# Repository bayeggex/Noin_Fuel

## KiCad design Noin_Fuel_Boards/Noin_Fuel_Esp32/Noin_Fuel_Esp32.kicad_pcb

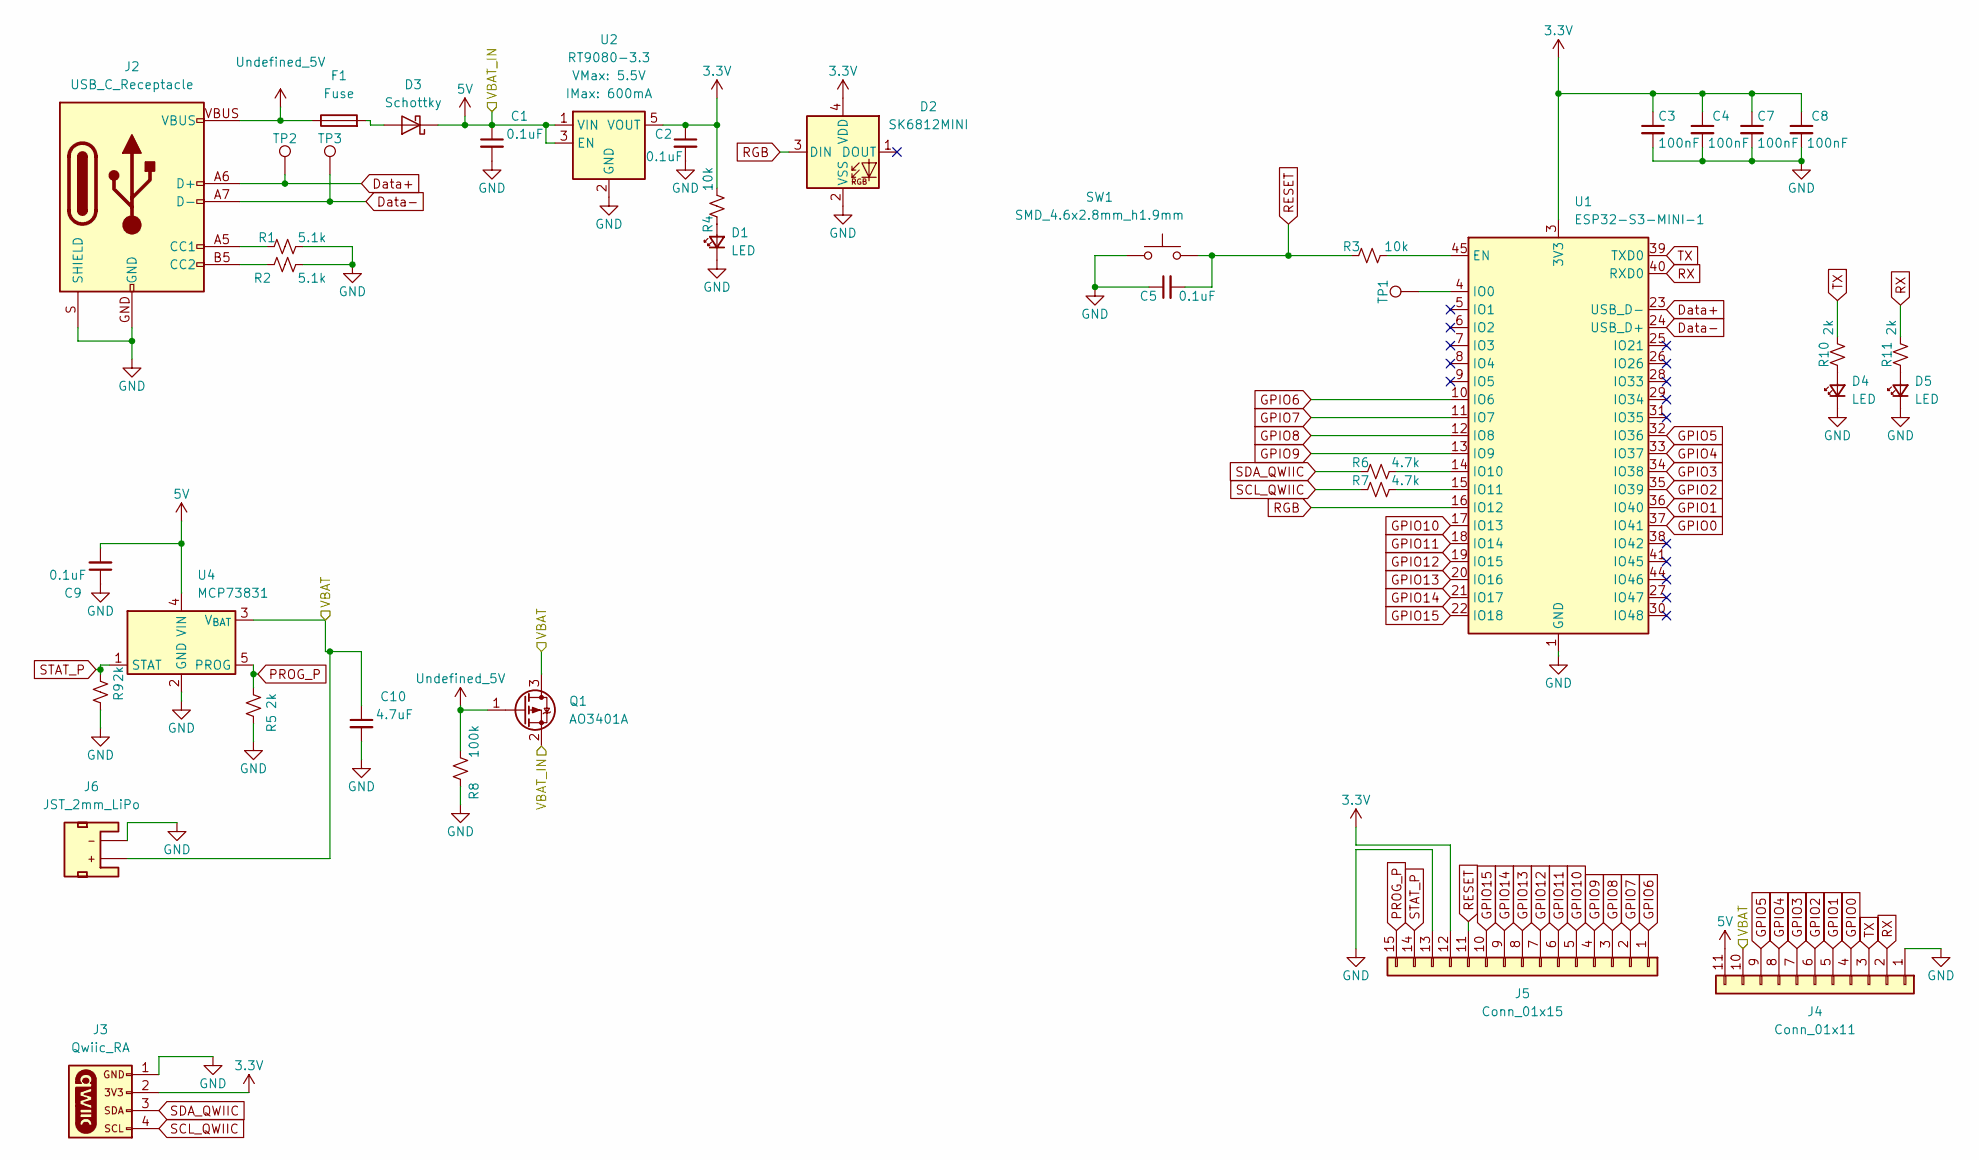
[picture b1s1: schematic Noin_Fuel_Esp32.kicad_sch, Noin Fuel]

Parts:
C1, C2, C5, C9: 0.1uF; C_0402_1005Metric; Voltage 25V; Tolerance 20%
C3, C4, C7, C8: 100nF; C_0402_1005Metric; Voltage 25V; Tolerance 20%
C10: 4.7uF; C_0402_1005Metric; Voltage 25V; Tolerance 20%
D1, D4, D5: LED; LED_0603_1608Metric
D2: SK6812MINI; LED_SK6812MINI_PLCC4_3.5x3.5mm_P1.75mm
D3: Schottky; Diode_Schottky_0603
F1: Fuse; Fuse_0603_1608Metric
J2: USB_C_Receptacle; USB-C_16
J3: Qwiic_RA; JST_1x04_P1.0mm_Horizontal_SMD
J4: Conn_01x11; 1x11_P2.54mm
J5: Conn_01x15; 1x15
J6: JST_2mm_LiPo; JST_1x02_P2.0mm_Horizontal_SMD
Q1: AO3401A; SOT-23
R1, R2: 5.1k; R_0402_1005Metric
R3, R4: 10k; R_0402_1005Metric
R5, R9, R10, R11: 2k; R_0402_1005Metric
R6, R7: 4.7k; R_0402_1005Metric
R8: 100k; R_0402_1005Metric
SW1: SMD_4.6x2.8mm_h1.9mm; Push_SMD_4.6x2.8mm_h1.9mm
TP1, TP2, TP3: 0.5mm; TestPoint-0.5mm
U1: ESP32-S3-MINI-1; ESP32-S2-MINI-1
U2: RT9080-3.3; SOT23-5
U4: MCP73831; SOT23-5

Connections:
3.3V: C2.1, C3.1, C4.1, C7.1, C8.1, D2.4 (VDD), J3.2, J5.12, R4.2, U1.3 (3V3), U2.5 (VOUT)
5V: C1.1, C9.2, D3.1 (K), J4.11, Q1.2 (S), U2.1 (VIN), U2.3 (EN), U4.4 (VIN)
/VBAT: C10.1, J4.10, J6.2 (+), Q1.3 (D), U4.3 (V_{BAT})
Data+: J2.A6 (D+), J2.B6 (D+), TP2.1, U1.23 (USB_D-)
Data-: J2.A7 (D-), J2.B7 (D-), TP3.1, U1.24 (USB_D+)
GND: C1.2, C2.2, C3.2, C4.2, C5.1, C7.2, C8.2, C9.1, C10.2, D1.1 (K), D2.2 (VSS), D4.1 (K), D5.1 (K), J2.GND, J2.S (SHIELD), J3.1, J4.1, J5.13, J6.1 (-), R1.2, R2.1, R5.2, R8.2, R9.2, SW1.1, U1.1 (GND), U1.2 (GND), U1.42 (GND), U1.43 (GND), U1.46 (GND), U1.47 (GND), U1.48 (GND), U1.49 (GND), U1.50 (GND), U1.51 (GND), U1.52 (GND), U1.53 (GND), U1.54 (GND), U1.55 (GND), U1.56 (GND), U1.57 (GND), U1.58 (GND), U1.59 (GND), U1.60 (GND), U1.61 (GND), U1.62 (GND), U1.63 (GND), U1.64 (GND), U1.65 (GND), U2.2 (GND), U4.2 (GND)
GPIO0: J4.4, U1.37 (IO41)
GPIO1: J4.5, U1.36 (IO40)
GPIO2: J4.6, U1.35 (IO39)
GPIO3: J4.7, U1.34 (IO38)
GPIO4: J4.8, U1.33 (IO37)
GPIO5: J4.9, U1.32 (IO36)
GPIO6: J5.1, U1.10 (IO6)
GPIO7: J5.2, U1.11 (IO7)
GPIO8: J5.3, U1.12 (IO8)
GPIO9: J5.4, U1.13 (IO9)
GPIO10: J5.5, U1.17 (IO13)
GPIO11: J5.6, U1.18 (IO14)
GPIO12: J5.7, U1.19 (IO15)
GPIO13: J5.8, U1.20 (IO16)
GPIO14: J5.9, U1.21 (IO17)
GPIO15: J5.10, U1.22 (IO18)
unnamed: D1.2 (A), R4.1
unnamed: D3.2 (A), F1.2
unnamed: D4.2 (A), R10.1
unnamed: D5.2 (A), R11.1
unnamed: J2.A5 (CC1), R1.1
unnamed: J2.B5 (CC2), R2.2
unnamed: R3.2, U1.45 (EN)
unnamed: TP1.1, U1.4 (IO0)
unnamed: R6.2, U1.14 (IO10)
unnamed: R7.2, U1.15 (IO11)
PROG_P: J5.15, R5.1, U4.5 (PROG)
RESET: C5.2, J5.11, R3.1, SW1.2
RGB: D2.3 (DIN), U1.16 (IO12)
RX: J4.2, R11.2, U1.40 (RXD0)
SCL_QWIIC: J3.4, R7.1
SDA_QWIIC: J3.3, R6.1
STAT_P: J5.14, R9.1, U4.1 (STAT)
TX: J4.3, R10.2, U1.39 (TXD0)
Undefined_5V: F1.1, J2.VBUS, Q1.1 (G), R8.1

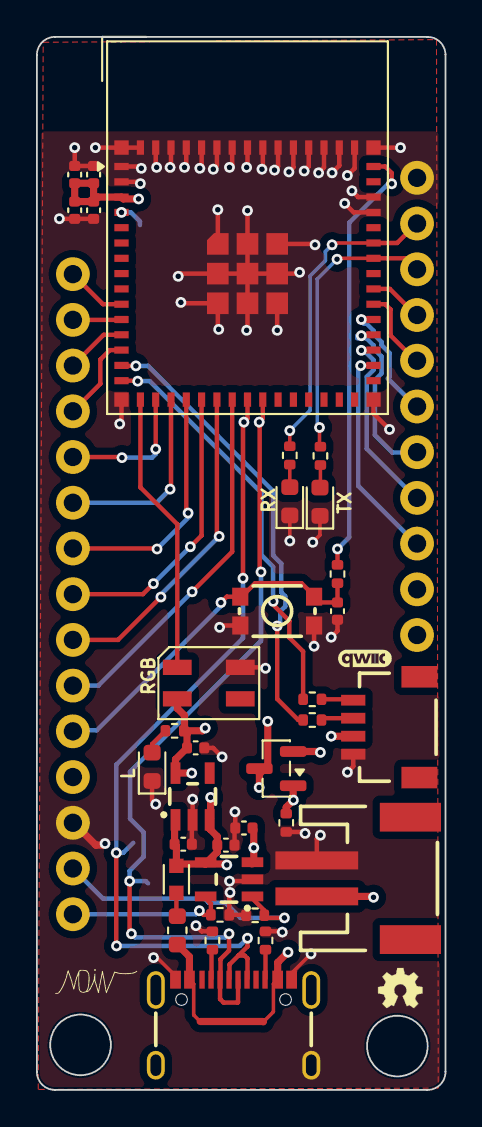
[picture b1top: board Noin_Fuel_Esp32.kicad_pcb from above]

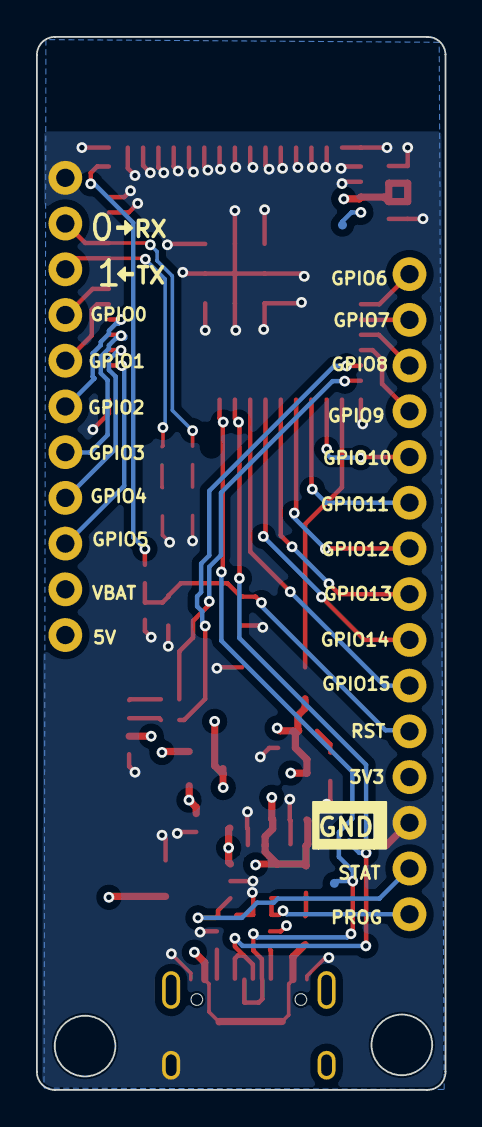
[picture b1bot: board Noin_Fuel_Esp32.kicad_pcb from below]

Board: 4 copper layers, 22.7 x 58.5 mm, 40 parts (3 on the bottom side), 41 nets.

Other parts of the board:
Ref**: Val**; OSHW_Logo_2.5mm

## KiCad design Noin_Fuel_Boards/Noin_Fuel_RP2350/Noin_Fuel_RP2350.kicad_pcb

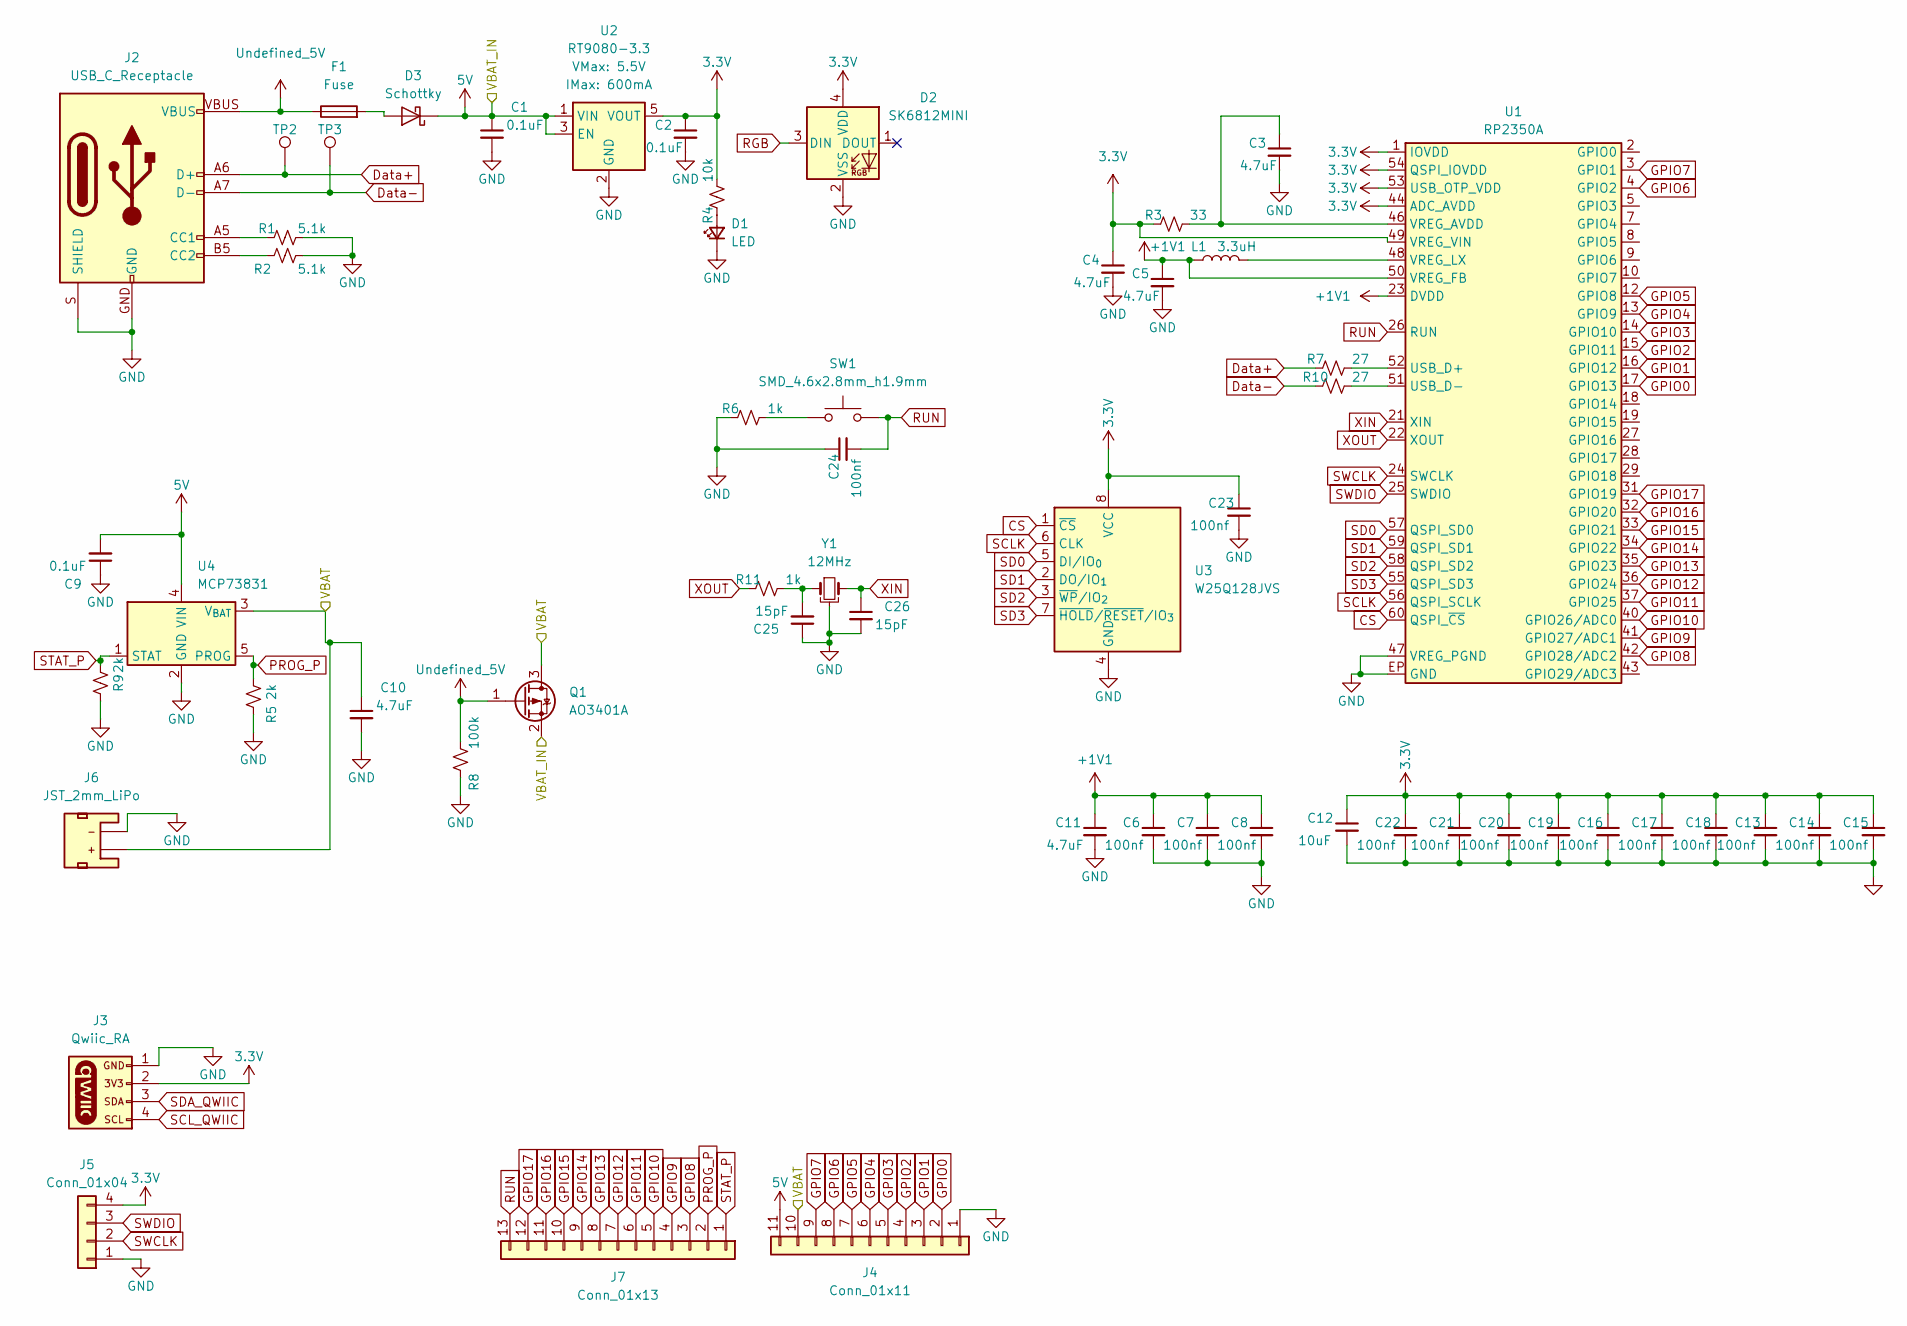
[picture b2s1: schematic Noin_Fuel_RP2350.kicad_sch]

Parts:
C1, C2, C9: 0.1uF; C_0402_1005Metric; Voltage 25V; Tolerance 20%
C3, C4, C5, C10, C11: 4.7uF; C_0402_1005Metric; Voltage 25V; Tolerance 20%
C6, C7, C8, C13, C14, C15, C16, C17, C18, C19, C20, C21, C22, C23, C24: 100nf; C_0402_1005Metric; Voltage 25V; Tolerance 20%
C12: 10uF; C_0402_1005Metric; Voltage 25V; Tolerance 20%
C25, C26: 15pF; C_0402_1005Metric; Voltage 25V; Tolerance 20%
D1: LED; LED_0603_1608Metric
D2: SK6812MINI; LED_SK6812MINI_PLCC4_3.5x3.5mm_P1.75mm
D3: Schottky; Diode_Schottky_0603
F1: Fuse; Fuse_0603_1608Metric
J2: USB_C_Receptacle; USB-C_16
J3: Qwiic_RA; JST_1x04_P1.0mm_Horizontal_SMD
J4: Conn_01x11; 1x11_P2.54mm
J5: Conn_01x04; 1x04_P2.54mm
J6: JST_2mm_LiPo; JST_1x02_P2.0mm_Horizontal_SMD
J7: Conn_01x13; 1x13
L1: 3.3uH; L_0402_1005Metric
Q1: AO3401A; SOT-23
R1, R2: 5.1k; R_0402_1005Metric
R3: 33; R_0402_1005Metric
R4: 10k; R_0402_1005Metric
R5, R9: 2k; R_0402_1005Metric
R6, R11: 1k; R_0402_1005Metric
R7, R10: 27; R_0402_1005Metric
R8: 100k; R_0402_1005Metric
SW1: SMD_4.6x2.8mm_h1.9mm; Push_SMD_4.6x2.8mm_h1.9mm
TP2, TP3: 0.5mm; TestPoint-0.5mm
U1: RP2350A; QFN-60-1EP_7x7mm_P0.4mm_EP3.5x3.5mm
U2: RT9080-3.3; SOT23-5
U3: W25Q128JVS; SOIC-8_5.3x5.3mm_P1.27mm
U4: MCP73831; SOT23-5
Y1: 12MHz; Crystal_SMD_2.5x2.0mm

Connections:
3.3V: C2.1, C4.1, C12.1, C13.1, C14.1, C15.1, C16.1, C17.1, C18.1, C19.1, C20.1, C21.1, C22.1, C23.1, D2.4 (VDD), J3.2, J5.4, R3.1, R4.2, U1.1 (IOVDD), U1.11 (IOVDD), U1.20 (IOVDD), U1.30 (IOVDD), U1.38 (IOVDD), U1.44 (ADC_AVDD), U1.45 (IOVDD), U1.49 (VREG_VIN), U1.53 (USB_OTP_VDD), U1.54 (QSPI_IOVDD), U2.5 (VOUT), U3.8 (VCC)
5V: C1.1, C9.2, D3.1 (K), J4.11, Q1.2 (S), U2.1 (VIN), U2.3 (EN), U4.4 (VIN)
+1V1: C5.1, C6.1, C7.1, C8.1, C11.1, L1.1, U1.6 (DVDD), U1.23 (DVDD), U1.39 (DVDD), U1.50 (VREG_FB)
/VBAT: C10.1, J4.10, J6.2 (+), Q1.3 (D), U4.3 (V_{BAT})
CS: U1.60 (QSPI_~CS), U3.1 (~CS)
Data+: J2.A6 (D+), J2.B6 (D+), R7.1, TP2.1 (1_1)
Data-: J2.A7 (D-), J2.B7 (D-), R10.1, TP3.1 (1_1)
GND: C1.2, C2.2, C3.2, C4.2, C5.2, C6.2, C7.2, C8.2, C9.1, C10.2, C11.2, C12.2, C13.2, C14.2, C15.2, C16.2, C17.2, C18.2, C19.2, C20.2, C21.2, C22.2, C23.2, C24.1, C25.1, C26.2, D1.1 (K), D2.2 (VSS), J2.GND, J2.S (SHIELD), J3.1, J4.1, J5.1, J6.1 (-), R1.2, R2.1, R5.2, R6.1, R8.2, R9.2, U1.47 (VREG_PGND), U1.EP (GND), U2.2 (GND), U3.4 (GND), U4.2 (GND), Y1.2, Y1.4
GPIO0: J4.2, U1.17 (GPIO13)
GPIO1: J4.3, U1.16 (GPIO12)
GPIO2: J4.4, U1.15 (GPIO11)
GPIO3: J4.5, U1.14 (GPIO10)
GPIO4: J4.6, U1.13 (GPIO9)
GPIO5: J4.7, U1.12 (GPIO8)
GPIO6: J4.8, U1.4 (GPIO2)
GPIO7: J4.9, U1.3 (GPIO1)
GPIO8: J7.3, U1.42 (GPIO28/ADC2)
GPIO9: J7.4, U1.41 (GPIO27/ADC1)
GPIO10: J7.5, U1.40 (GPIO26/ADC0)
GPIO11: J7.6, U1.37 (GPIO25)
GPIO12: J7.7, U1.36 (GPIO24)
GPIO13: J7.8, U1.35 (GPIO23)
GPIO14: J7.9, U1.34 (GPIO22)
GPIO15: J7.10, U1.33 (GPIO21)
GPIO16: J7.11, U1.32 (GPIO20)
GPIO17: J7.12, U1.31 (GPIO19)
unnamed: C25.2, R11.2, Y1.1
unnamed: D1.2 (A), R4.1
unnamed: D3.2 (A), F1.2
unnamed: J2.A5 (CC1), R1.1
unnamed: J2.B5 (CC2), R2.2
unnamed: R6.2, SW1.1
unnamed: R7.2, U1.52 (USB_D+)
unnamed: R10.2, U1.51 (USB_D-)
unnamed: C3.1, R3.2, U1.46 (VREG_AVDD)
unnamed: L1.2, U1.48 (VREG_LX)
PROG_P: J7.2, R5.1, U4.5 (PROG)
RGB: D2.3 (DIN)
RUN: C24.2, J7.13, SW1.2, U1.26 (RUN)
SCLK: U1.56 (QSPI_SCLK), U3.6 (CLK)
SCL_QWIIC: J3.4
SD0: U1.57 (QSPI_SD0), U3.5 (DI/IO_{0})
SD1: U1.59 (QSPI_SD1), U3.2 (DO/IO_{1})
SD2: U1.58 (QSPI_SD2), U3.3 (~WP/IO_{2})
SD3: U1.55 (QSPI_SD3), U3.7 (~HOLD/~RESET/IO_{3})
SDA_QWIIC: J3.3
STAT_P: J7.1, R9.1, U4.1 (STAT)
SWCLK: J5.2, U1.24 (SWCLK)
SWDIO: J5.3, U1.25 (SWDIO)
Undefined_5V: F1.1, J2.VBUS, Q1.1 (G), R8.1
XIN: C26.1, U1.21 (XIN), Y1.3
XOUT: R11.1, U1.22 (XOUT)

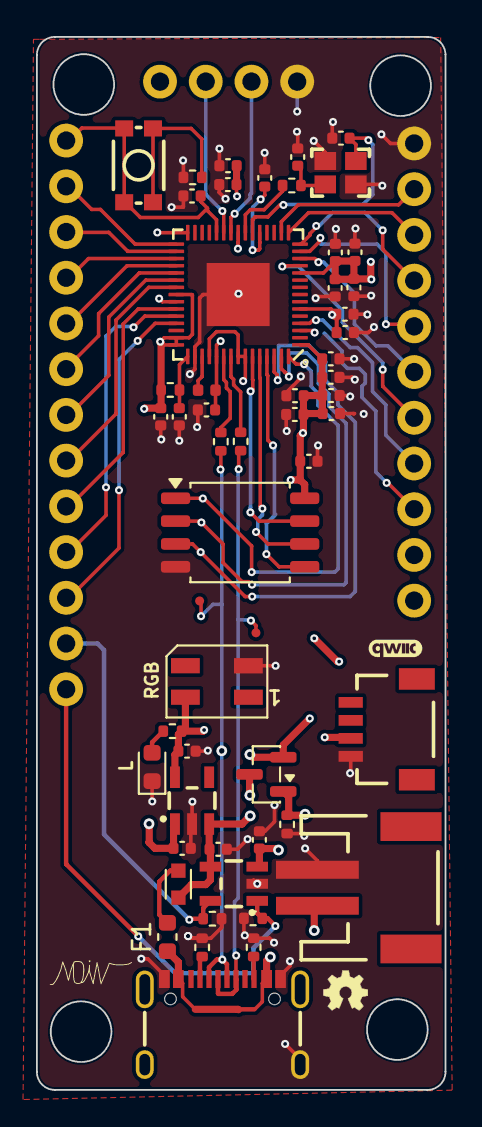
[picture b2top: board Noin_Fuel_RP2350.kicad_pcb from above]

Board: 4 copper layers, 22.7 x 58.5 mm, 58 parts (0 on the bottom side), 49 nets.

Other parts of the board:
Ref**: Val**; OSHW_Logo_2.5mm

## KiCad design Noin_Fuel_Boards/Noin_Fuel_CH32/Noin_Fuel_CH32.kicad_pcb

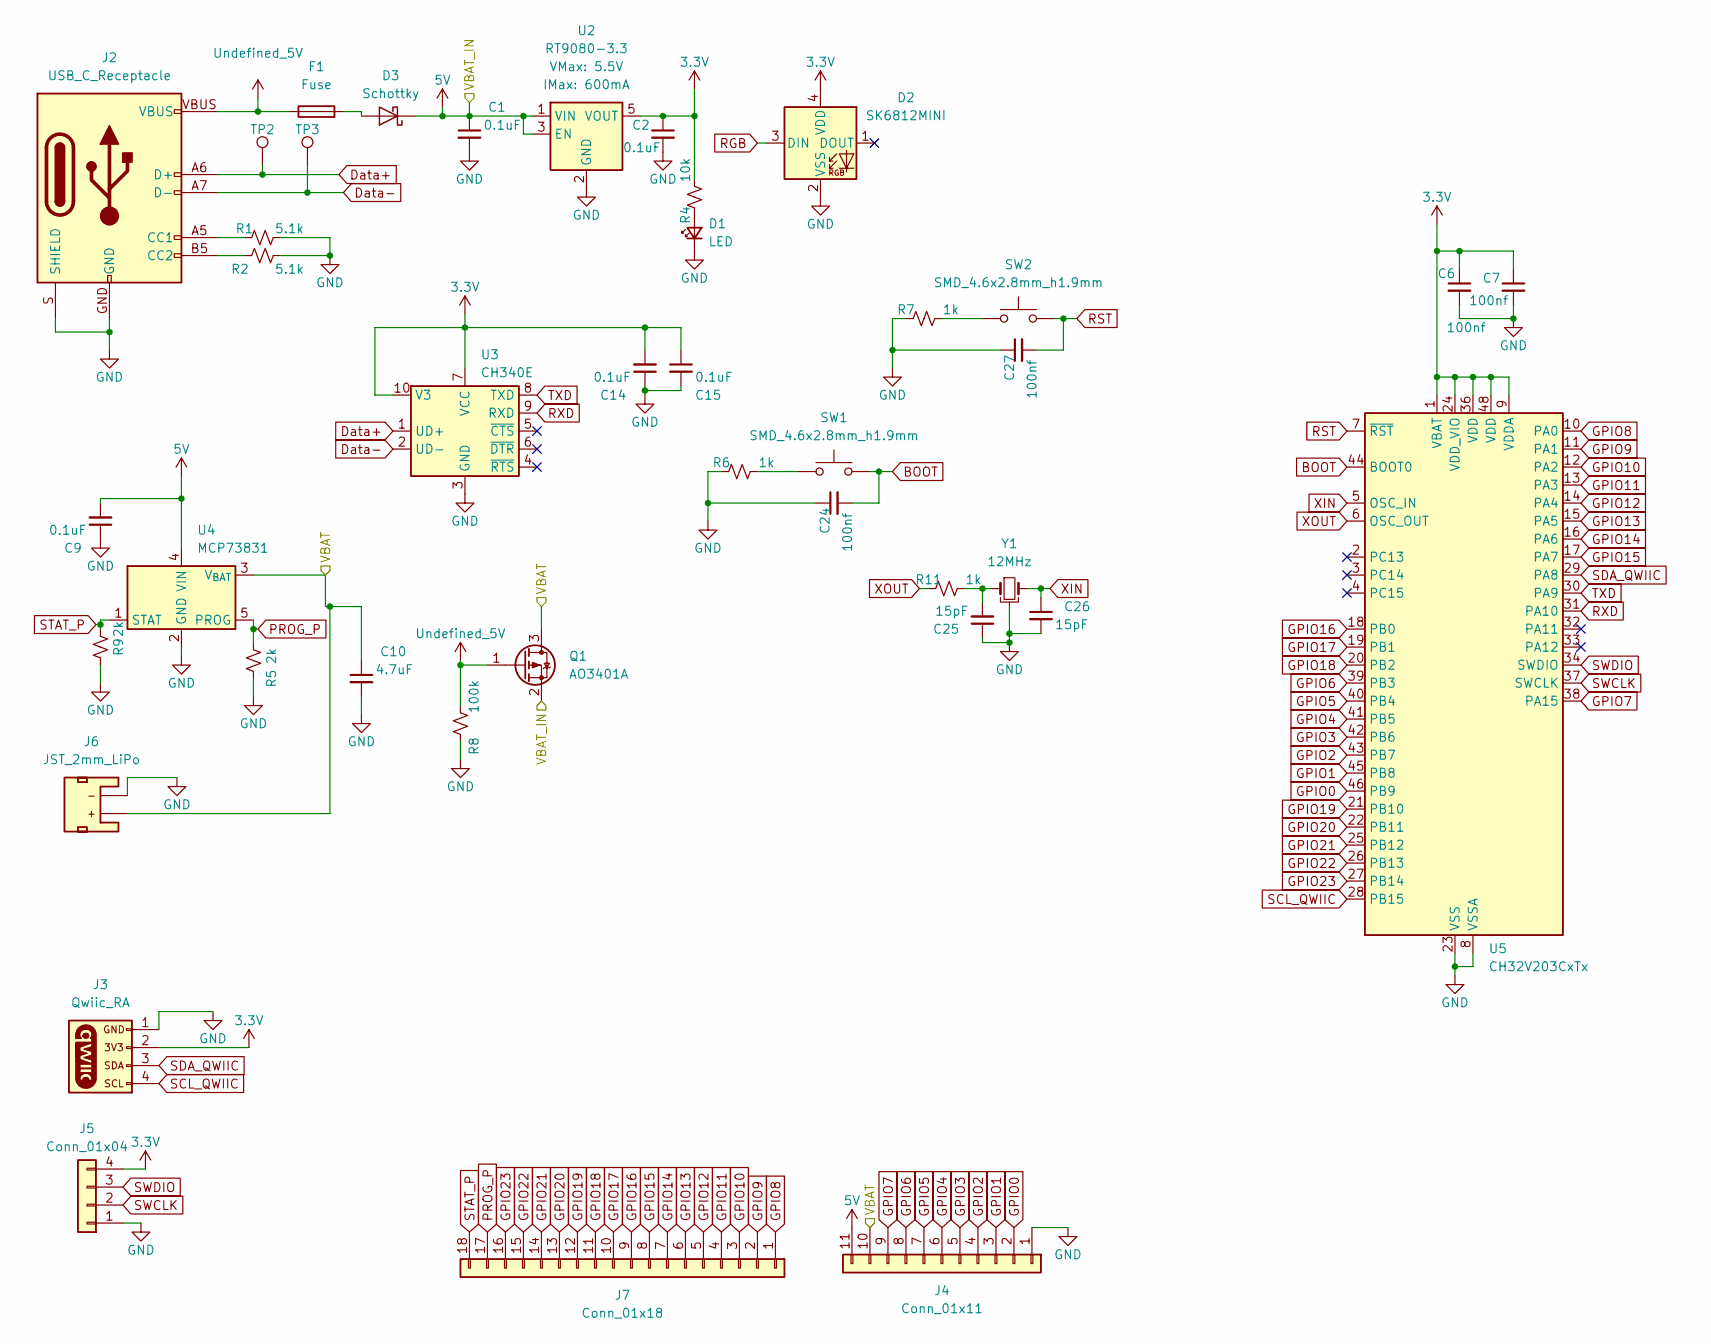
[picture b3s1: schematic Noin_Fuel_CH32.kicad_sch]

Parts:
C1, C2, C9, C14, C15: 0.1uF; C_0402_1005Metric; Voltage 25V; Tolerance 20%
C6, C7, C24, C27: 100nf; C_0402_1005Metric; Voltage 25V; Tolerance 20%
C10: 4.7uF; C_0402_1005Metric; Voltage 25V; Tolerance 20%
C25, C26: 15pF; C_0402_1005Metric; Voltage 25V; Tolerance 20%
D1: LED; LED_0603_1608Metric
D2: SK6812MINI; LED_SK6812MINI_PLCC4_3.5x3.5mm_P1.75mm
D3: Schottky; Diode_Schottky_0603
F1: Fuse; Fuse_0603_1608Metric
J2: USB_C_Receptacle; USB-C_16
J3: Qwiic_RA; JST_1x04_P1.0mm_Horizontal_SMD
J4: Conn_01x11; 1x11_P2.54mm
J5: Conn_01x04; 1x04_P2.54mm
J6: JST_2mm_LiPo; JST_1x02_P2.0mm_Horizontal_SMD
J7: Conn_01x18; 1x18
Q1: AO3401A; SOT-23
R1, R2: 5.1k; R_0402_1005Metric
R4: 10k; R_0402_1005Metric
R5, R9: 2k; R_0402_1005Metric
R6, R7, R11: 1k; R_0402_1005Metric
R8: 100k; R_0402_1005Metric
SW1, SW2: SMD_4.6x2.8mm_h1.9mm; Push_SMD_4.6x2.8mm_h1.9mm
TP2, TP3: 0.5mm; TestPoint-0.5mm
U2: RT9080-3.3; SOT23-5
U3: CH340E; MSOP-10_3x3mm_P0.5mm
U4: MCP73831; SOT23-5
U5: CH32V203CxTx; LQFP-48_7x7mm_P0.5mm
Y1: 12MHz; Crystal_SMD_2.5x2.0mm

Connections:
3.3V: C2.1, C6.1, C7.1, C14.2, C15.1, D2.4 (VDD), J3.2, J5.4, R4.2, U2.5 (VOUT), U3.7 (VCC), U3.10 (V3), U5.1 (VBAT), U5.9 (VDDA), U5.24 (VDD_VIO), U5.36 (VDD), U5.48 (VDD)
5V: C1.1, C9.2, D3.1 (K), J4.11, Q1.2 (S), U2.1 (VIN), U2.3 (EN), U4.4 (VIN)
/VBAT: C10.1, J4.10, J6.2 (+), Q1.3 (D), U4.3 (V_{BAT})
BOOT: C24.2, SW1.2, U5.44 (BOOT0)
Data+: J2.A6 (D+), J2.B6 (D+), TP2.1 (1_1), U3.1 (UD+)
Data-: J2.A7 (D-), J2.B7 (D-), TP3.1 (1_1), U3.2 (UD-)
GND: C1.2, C2.2, C6.2, C7.2, C9.1, C10.2, C14.1, C15.2, C24.1, C25.1, C26.2, C27.1, D1.1 (K), D2.2 (VSS), J2.GND, J2.S (SHIELD), J3.1, J4.1, J5.1, J6.1 (-), R1.2, R2.1, R5.2, R6.1, R7.1, R8.2, R9.2, U2.2 (GND), U3.3 (GND), U4.2 (GND), U5.8 (VSSA), U5.23 (VSS), U5.35 (VSS), U5.47 (VSS), Y1.2, Y1.4
GPIO0: J4.2, U5.46 (PB9)
GPIO1: J4.3, U5.45 (PB8)
GPIO2: J4.4, U5.43 (PB7)
GPIO3: J4.5, U5.42 (PB6)
GPIO4: J4.6, U5.41 (PB5)
GPIO5: J4.7, U5.40 (PB4)
GPIO6: J4.8, U5.39 (PB3)
GPIO7: J4.9, U5.38 (PA15)
GPIO8: J7.1, U5.10 (PA0)
GPIO9: J7.2, U5.11 (PA1)
GPIO10: J7.3, U5.12 (PA2)
GPIO11: J7.4, U5.13 (PA3)
GPIO12: J7.5, U5.14 (PA4)
GPIO13: J7.6, U5.15 (PA5)
GPIO14: J7.7, U5.16 (PA6)
GPIO15: J7.8, U5.17 (PA7)
GPIO16: J7.9, U5.18 (PB0)
GPIO17: J7.10, U5.19 (PB1)
GPIO18: J7.11, U5.20 (PB2)
GPIO19: J7.12, U5.21 (PB10)
GPIO20: J7.13, U5.22 (PB11)
GPIO21: J7.14, U5.25 (PB12)
GPIO22: J7.15, U5.26 (PB13)
GPIO23: J7.16, U5.27 (PB14)
unnamed: C25.2, R11.2, Y1.1
unnamed: D1.2 (A), R4.1
unnamed: D3.2 (A), F1.2
unnamed: J2.A5 (CC1), R1.1
unnamed: J2.B5 (CC2), R2.2
unnamed: R6.2, SW1.1
unnamed: R7.2, SW2.1
PROG_P: J7.17, R5.1, U4.5 (PROG)
RGB: D2.3 (DIN)
RST: C27.2, SW2.2, U5.7 (~RST)
RXD: U3.9 (RXD), U5.31 (PA10)
SCL_QWIIC: J3.4, U5.28 (PB15)
SDA_QWIIC: J3.3, U5.29 (PA8)
STAT_P: J7.18, R9.1, U4.1 (STAT)
SWCLK: J5.2, U5.37 (SWCLK)
SWDIO: J5.3, U5.34 (SWDIO)
TXD: U3.8 (TXD), U5.30 (PA9)
Undefined_5V: F1.1, J2.VBUS, Q1.1 (G), R8.1
XIN: C26.1, U5.5 (OSC_IN), Y1.3
XOUT: R11.1, U5.6 (OSC_OUT)

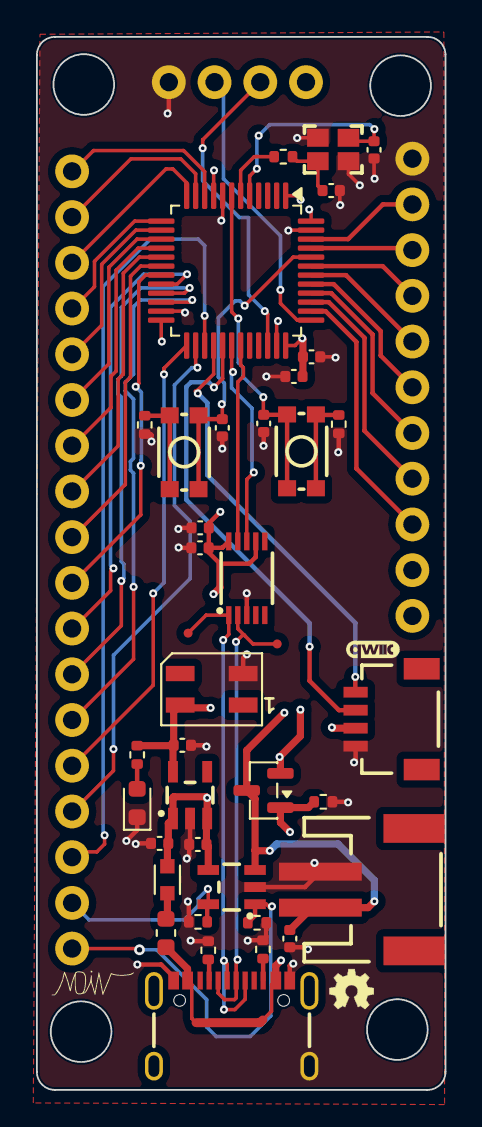
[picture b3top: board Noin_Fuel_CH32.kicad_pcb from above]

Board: 4 copper layers, 22.7 x 58.5 mm, 42 parts (0 on the bottom side), 50 nets.

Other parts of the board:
Ref**: Val**; OSHW_Logo_2.5mm

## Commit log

2026-04-18 Change license from Apache 2.0 to CERN OHL-S
    Replaced Apache License 2.0 with CERN Open Hardware License Version 2 - Strongly Reciprocal. Updated terms and conditions to reflect the new license.
2026-04-19 Noin_Fuel_Family_Board_Pcb_Update
2026-04-20 IDE Push
